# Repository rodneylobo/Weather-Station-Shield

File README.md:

# Weather-Station-Shield
This Arduino Nano shield was used in developing Weather Stations
It used  Humidity sensor, Carbon dioxide sensor, Light intensity sensor (photoresistor), Air Pressure sensor and Temperature sensor.
All of these can be displayed using the LCD
It also uses a bluetooth to wirelessely send the collected data to cell phones.
All that needs to be done is etch the pcb, and solder appropriate components.
Components required:
  1. FR1 boards (FR4 are better, actually)
  2. Female Header pins
  3. 16X2 LCD
  4. Trimpot (103 or above)
  5. 2.5 mm DC female jack
  6. Resistors (x3)
  7. 3mm LED (x2)
  8. Arduino Nano
  9. Photoresistor
  10. DHT11 (humidity sensor)
  11. BMP180 (air pressure sensor)
  12. MQ135 (carbon dioxide/ Air Quality sensor)
  13. LM35 (temperature sensor)
  14. Bluetooth module (HC05 or HC06)
  15. 9V battery and battery connector
  16. 2.5mm male DC jack
  17. Single strand wires
  18. Solder and soldering iron

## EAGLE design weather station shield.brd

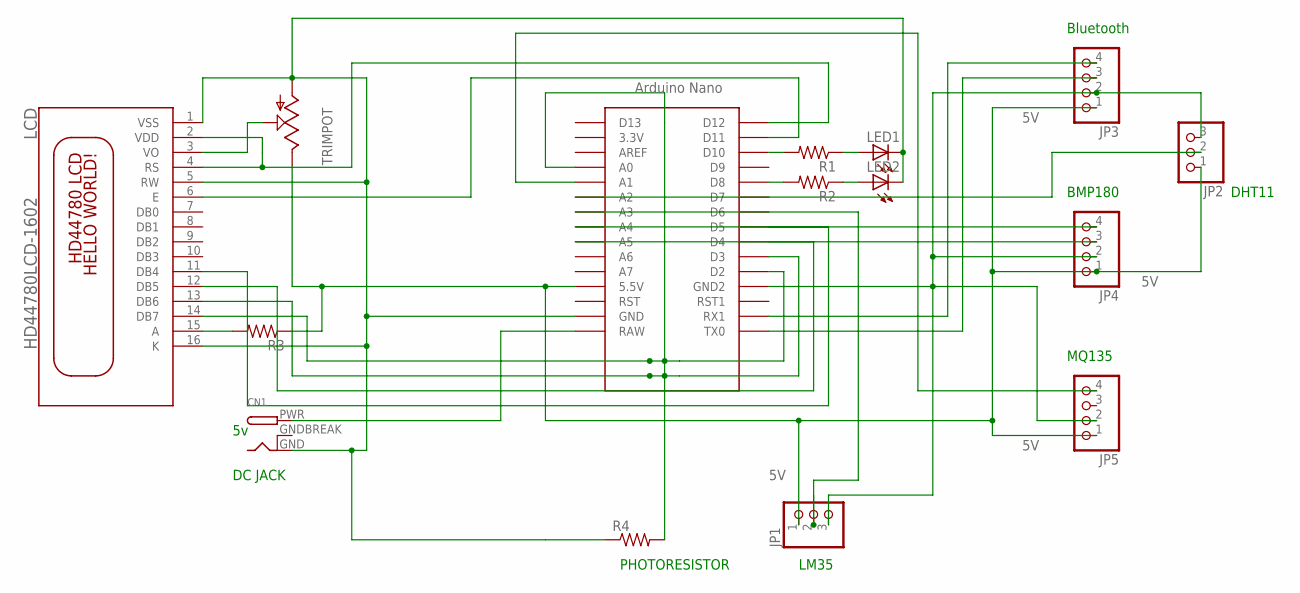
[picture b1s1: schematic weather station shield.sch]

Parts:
CN1: DCBARRELPTH; DCJACK_2MM_PTH
JP1, JP2: PINHD-1X3; 1X03
JP3, JP4, JP5: PINHD-1X4; 1X04
LCD: HD44780LCD-1602; LCD1602
LED1, LED2: LED5MM
R1, R2, R3, R4: R-US_0204/7; 0204/7
TRIMPOT: TRIM_US-CA6V; CA6V
U$1: NANO

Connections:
5V: JP1.1, JP2.1, JP3.1, JP4.1, JP5.1, R3.1, TRIMPOT.E, U$1.5V (5.5V)
GNDBREAK: CN1.GNDBREAK
unnamed: LCD.13 (DB6), U$1.D3, U$1.ICSP1, U$1.ICSP3, U$1.ICSP5
unnamed: LCD.12 (DB5), U$1.D4
unnamed: LCD.3 (VO), TRIMPOT.S
unnamed: JP2.2, U$1.A2
unnamed: LCD.6 (E), U$1.D11
unnamed: LCD.15 (A), R3.2
unnamed: LCD.11 (DB4), U$1.D5
unnamed: JP3.4, U$1.RX1
unnamed: JP3.3, U$1.TX0
unnamed: JP4.4, U$1.A4
unnamed: JP4.3, U$1.A5
unnamed: R1.2, U$1.D10
unnamed: LED1.A, R1.1
unnamed: R2.2, U$1.D8
unnamed: LED2.A, R2.1
unnamed: R4.2, U$1.A0
unnamed: JP1.3, JP2.3, JP3.2, JP4.2, JP5.2, U$1.GND1 (GND2)
unnamed: JP5.4, U$1.A1
unnamed: LCD.14 (DB7), U$1.D2, U$1.ICSP2, U$1.ICSP4, U$1.ICSP6
unnamed: JP1.2, U$1.A3
unnamed: CN1.PWR, U$1.RAW
VDD: LCD.2 (VDD), LCD.4 (RS), U$1.D12
VSS: CN1.GND, LCD.1 (VSS), LCD.5 (RW), LCD.16 (K), LED1.K (C), LED2.K (C), R4.1, TRIMPOT.A, U$1.GND

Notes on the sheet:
Bluetooth
BMP180
MQ135
DHT11
LM35
PHOTORESISTOR
DC JACK

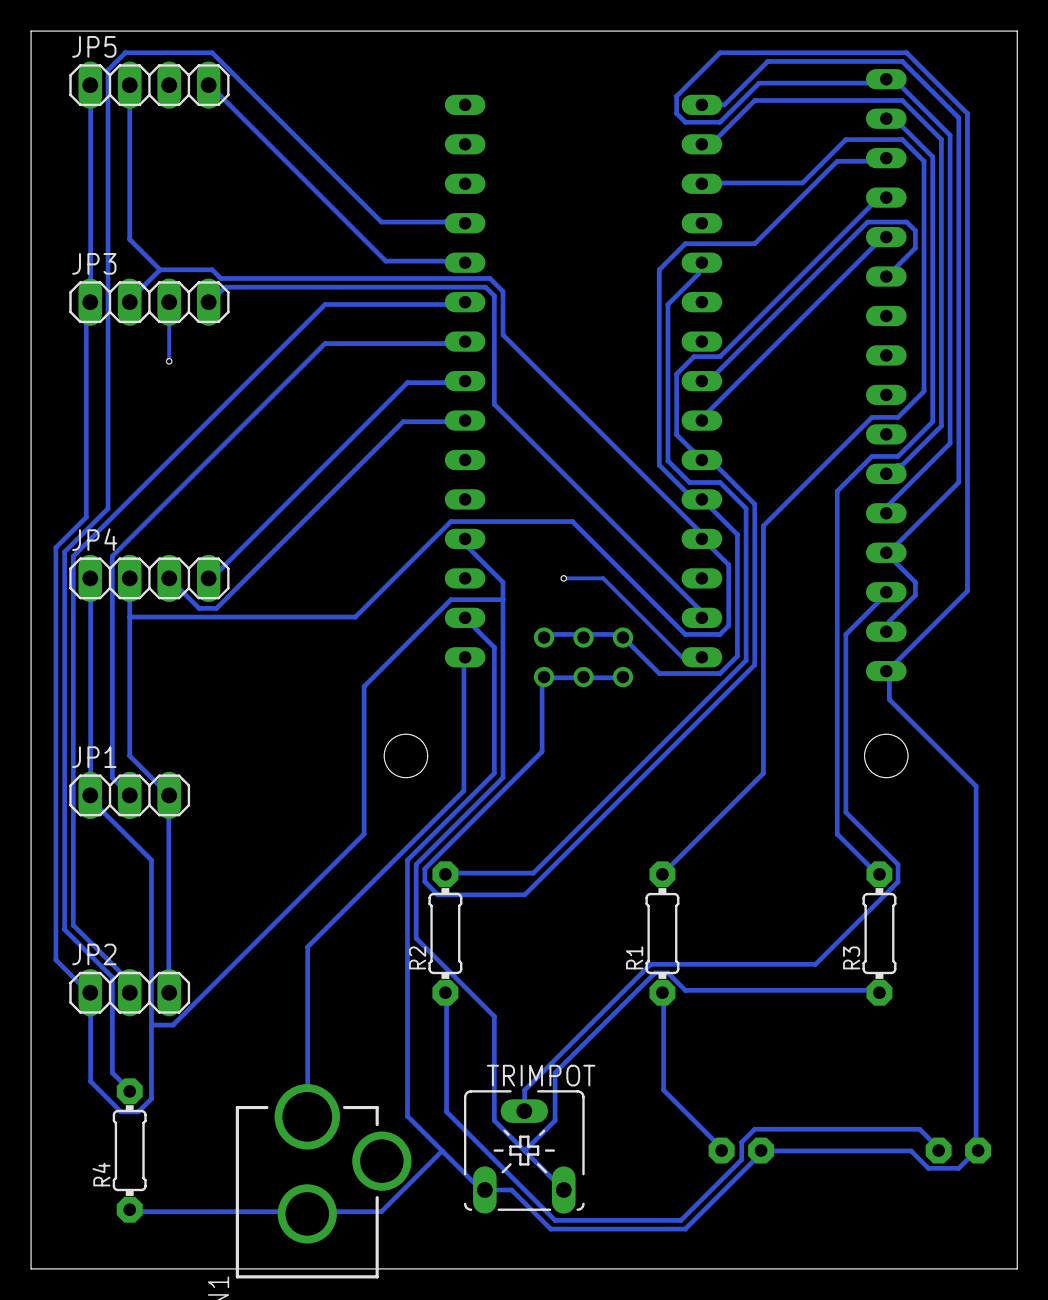
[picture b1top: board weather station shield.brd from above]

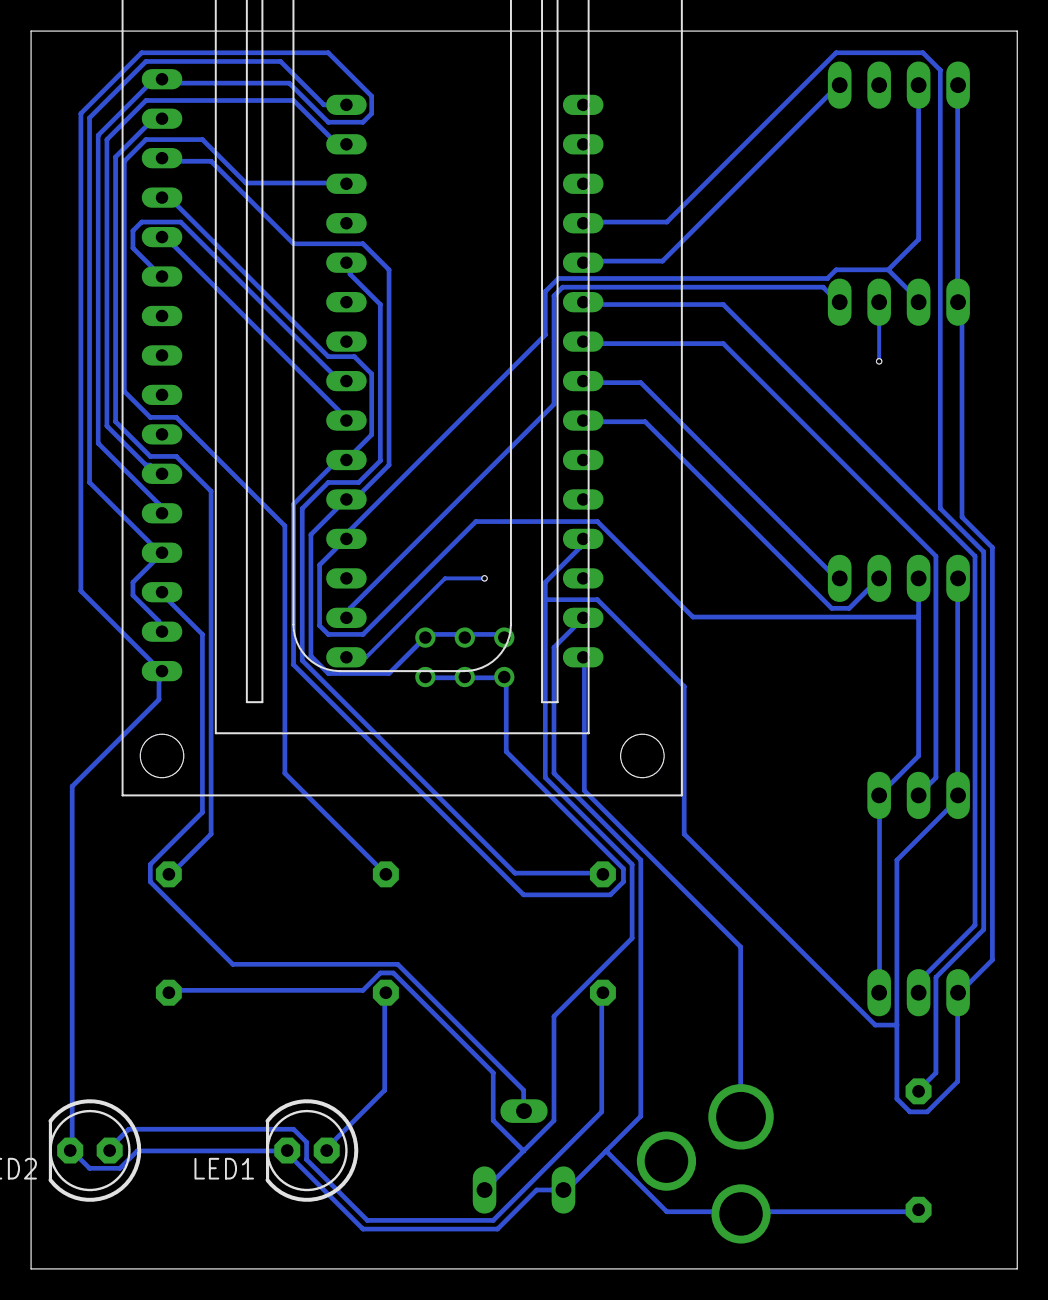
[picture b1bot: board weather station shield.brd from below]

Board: 2 copper layers, 63.5 x 79.7 mm, 15 parts (3 on the bottom side), 24 nets.

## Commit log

2018-10-08 Add files via upload
    Project files and pdf added
2018-10-08 Update README.md
    Components added
2018-10-08 Add files via upload
    Arduino sketch added
